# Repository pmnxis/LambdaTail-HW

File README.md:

# LambdaTail PCB

**Open source IoT node for arcade game**

The goal of this repository is to make **Rust** + **RISC-V** + **Kicad6** based hardware.
And IoT node should be published to large number of devices. So aimed to manufacture with low-cost with less-BOM.

## How works
Monitor vend side device such as paper or coin acceptor at top connector. And then reflect or modify signal to bottom side's connector. 

While monitor vend side, send signal to server or process something.

## Schematics
[Schematic](doc/LambdaTail-HW.pdf)

## Simplified characteristics
| Parameter | Min | Typ | Max | Unit | 
| --- | --- | --- | --- | --- |
| Voltage Power Supply | 4.5 | 12  | 16  | V  |
| Current Consumption  | 50  | 100 | 400 | mA |
| Dimenssion | | 55 x 55 x 16 | | mm

## Dependancy of footprint library
 - https://github.com/pmnxis/Lambda_KICAD5_LIB
 - https://github.com/espressif/kicad-libraries
 - Kicad 5.99 (Kicad 6) and Kicad 5 (legacy) default libraries.

## License
CERN-OHL-S-2.0 for Routing, Gerber, Schematic

Follow to original owner's license for footprint and related things.

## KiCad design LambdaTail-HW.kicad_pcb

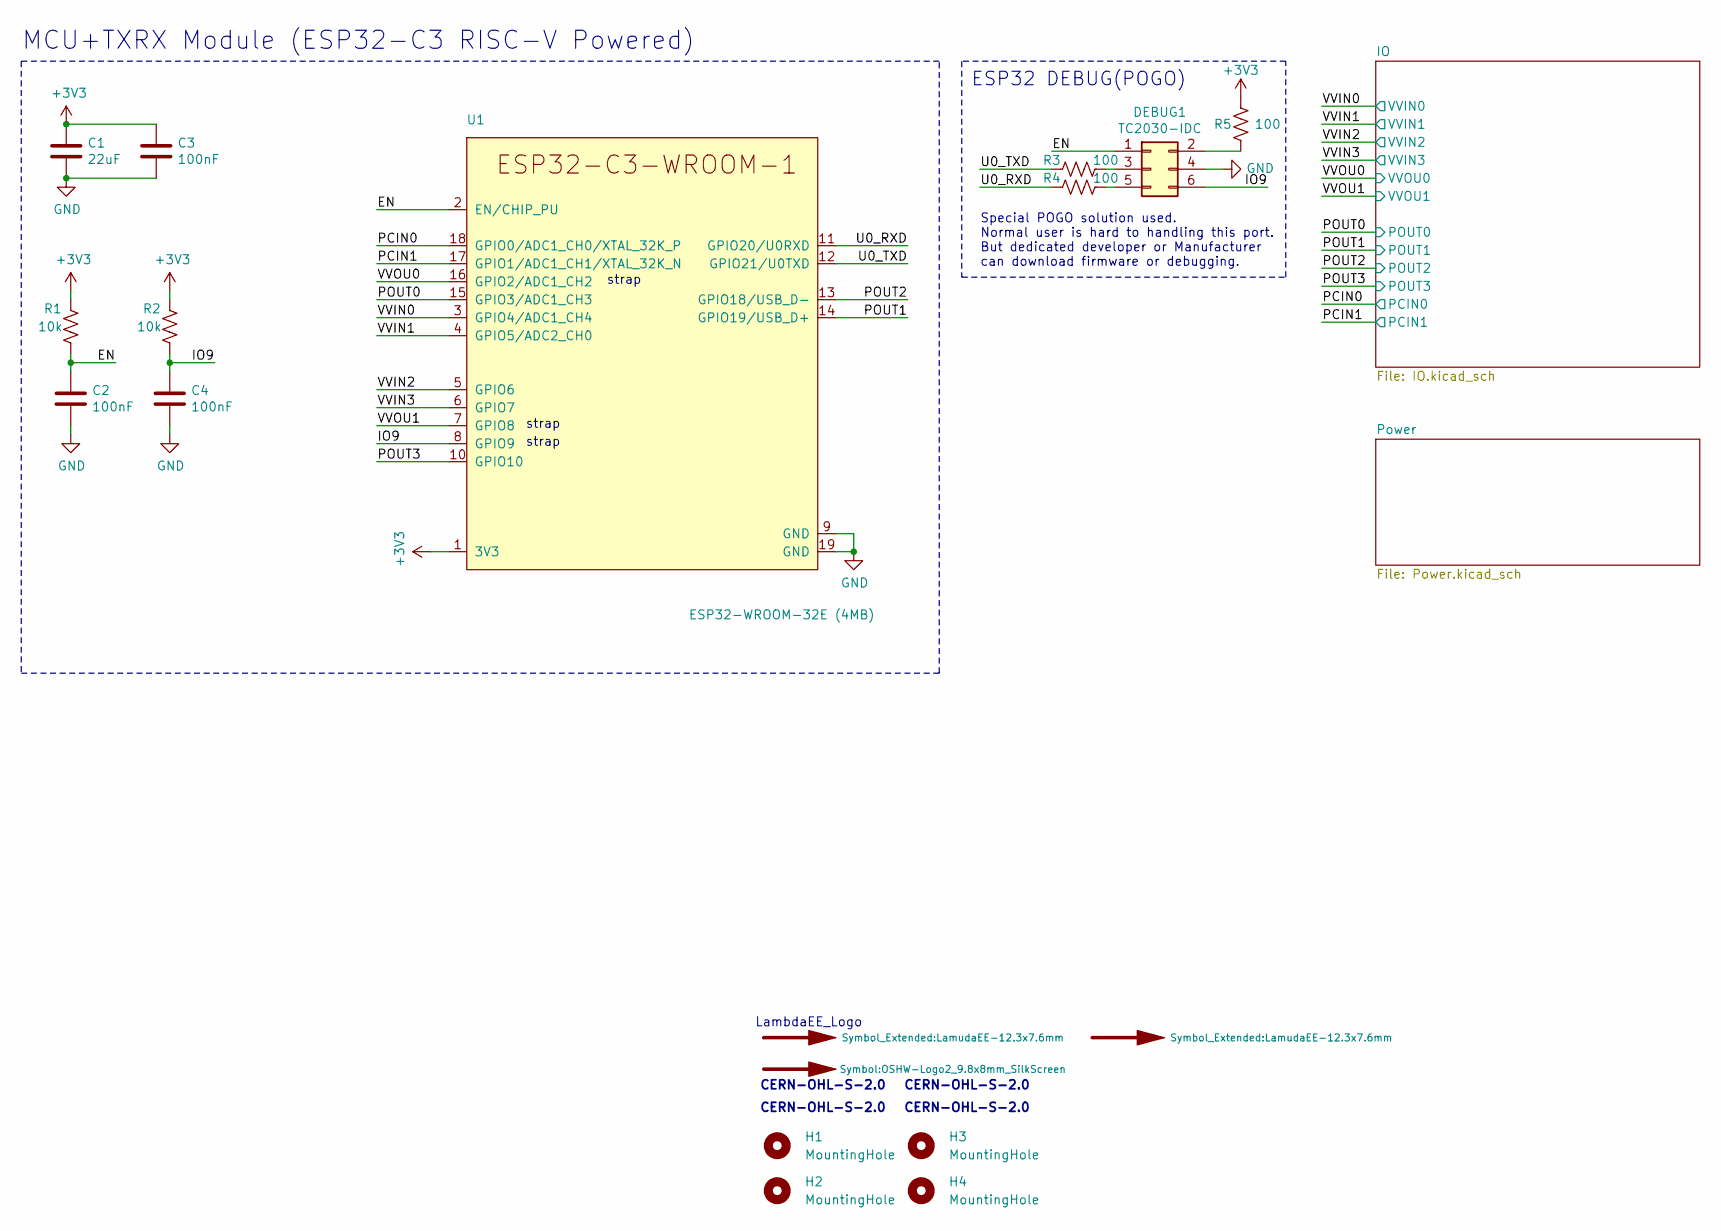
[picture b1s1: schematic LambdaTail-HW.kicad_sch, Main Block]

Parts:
C1: 22uF; C_0805_2012Metric; MFR.Part# CL21A226MAQNNNE; LCSC Part C45783
C2, C3, C4: 100nF; C_0402_1005Metric; MFR.Part# CL05B104KO5NNNC; LCSC Part C1525
DEBUG1: TC2030-IDC; Tag-Connect_TC2030-IDC-FP_2x03_P1.27mm_Vertical
H1, H2, H3, H4: MountingHole; MountingHole_4.3mm_M4_ISO7380_Pad_TopBottom
R1, R2: 10k; R_0402_1005Metric; MFR.Part# 0402WGF1002TCE; LCSC Part C25744
R3, R4, R5: 100; R_0402_1005Metric; MFR.Part# 0402WGF1000TCE; LCSC Part C25076
SYM1, SYM3: SYM_Arrow_XLarge; LamudaEE-12.3x7.6mm
SYM2: SYM_Arrow_XLarge; OSHW-Logo2_9.8x8mm_SilkScreen
U1: ESP32-WROOM-32E (4MB); ESP32-C3-WROOM-1; MFR.Part# ESP32-WROOM-32E (4MB)

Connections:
/EN: C2.1, DEBUG1.1, R1.2, U1.2 (EN/CHIP_PU)
/IO9: C4.1, DEBUG1.6, R2.2, U1.8 (GPIO9)
/PCIN0: U1.18 (GPIO0/ADC1_CH0/XTAL_32K_P); also elsewhere on the board
/PCIN1: U1.17 (GPIO1/ADC1_CH1/XTAL_32K_N); also elsewhere on the board
/POUT0: U1.15 (GPIO3/ADC1_CH3); also elsewhere on the board
/POUT1: U1.14 (GPIO19/USB_D+); also elsewhere on the board
/POUT2: U1.13 (GPIO18/USB_D-); also elsewhere on the board
/POUT3: U1.10 (GPIO10); also elsewhere on the board
/U0_RXD: R4.1, U1.11 (GPIO20/U0RXD)
/U0_TXD: R3.1, U1.12 (GPIO21/U0TXD)
/VVIN0: U1.3 (GPIO4/ADC1_CH4); also elsewhere on the board
/VVIN1: U1.4 (GPIO5/ADC2_CH0); also elsewhere on the board
/VVIN2: U1.5 (GPIO6); also elsewhere on the board
/VVIN3: U1.6 (GPIO7); also elsewhere on the board
/VVOU0: U1.16 (GPIO2/ADC1_CH2); also elsewhere on the board
/VVOU1: U1.7 (GPIO8); also elsewhere on the board
GND: C1.2, C2.2, C3.2, C4.2, DEBUG1.4, U1.9 (GND), U1.19 (GND); also elsewhere on the board
unnamed: DEBUG1.2, R5.2
unnamed: DEBUG1.3, R3.2
unnamed: DEBUG1.5, R4.2

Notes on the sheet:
MCU+TXRX Module (ESP32-C3 RISC-V Powered)
strap
LambdaEE_Logo
CERN-OHL-S-2.0
ESP32 DEBUG(POGO)
Special POGO solution used. Normal user is hard to handling this port. But dedicated developer or Manufacturer can download firmware or debugging.

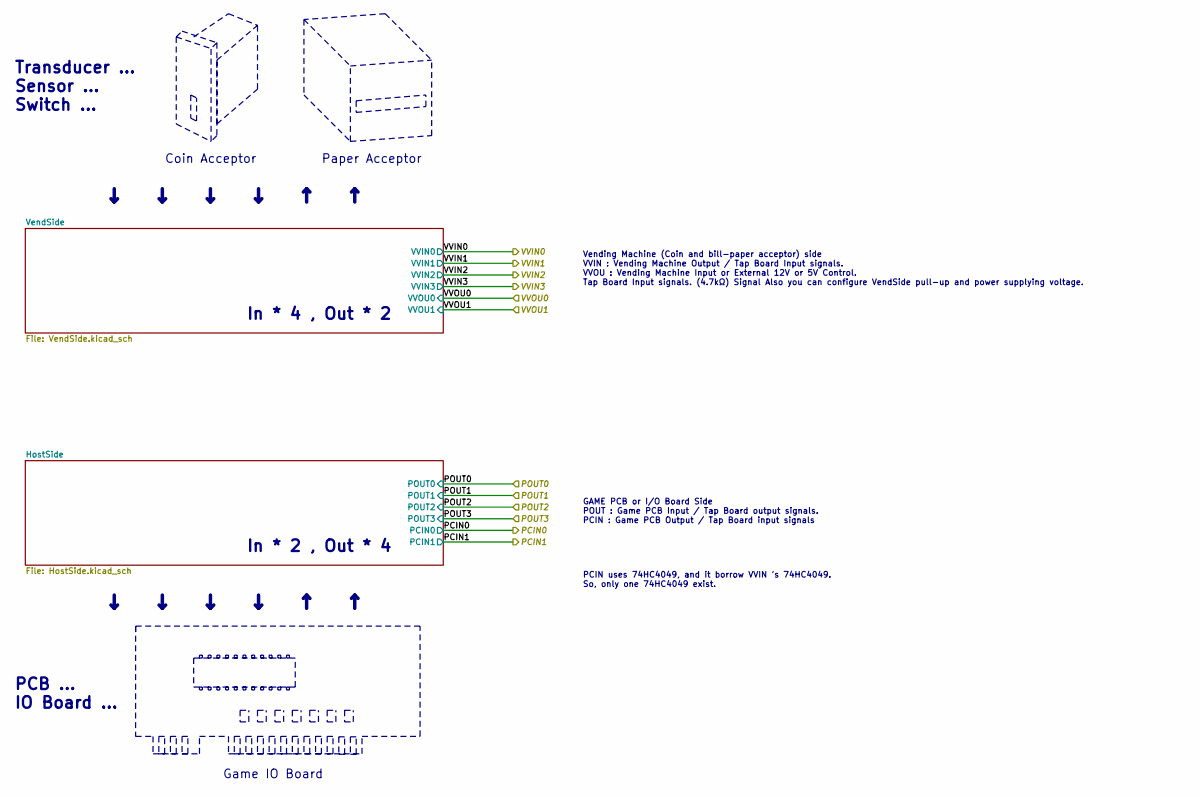
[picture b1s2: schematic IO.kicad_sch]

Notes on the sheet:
Transducer ... Sensor ... Switch ...
PCB ... IO Board ...
Coin Acceptor
Game IO Board
In * 4 , Out * 2
In * 2 , Out * 4
Paper Acceptor
↓ ↓ ↓ ↓ ↑ ↑
Vending Machine (Coin and bill-paper acceptor) side VVIN : Vending Machine Output / Tap Board Input signals. VVOU : Vending Machine Input or External 12V or 5V Control. Tap Board Input signals. (4.7kΩ) Signal Also you can configure VendSide pull-up and power supplying voltage.
GAME PCB or I/O Board Side POUT : Game PCB Input / Tap Board output signals. PCIN : Game PCB Output / Tap Board input signals
PCIN uses 74HC4049, and it borrow VVIN 's 74HC4049. So, only one 74HC4049 exist.

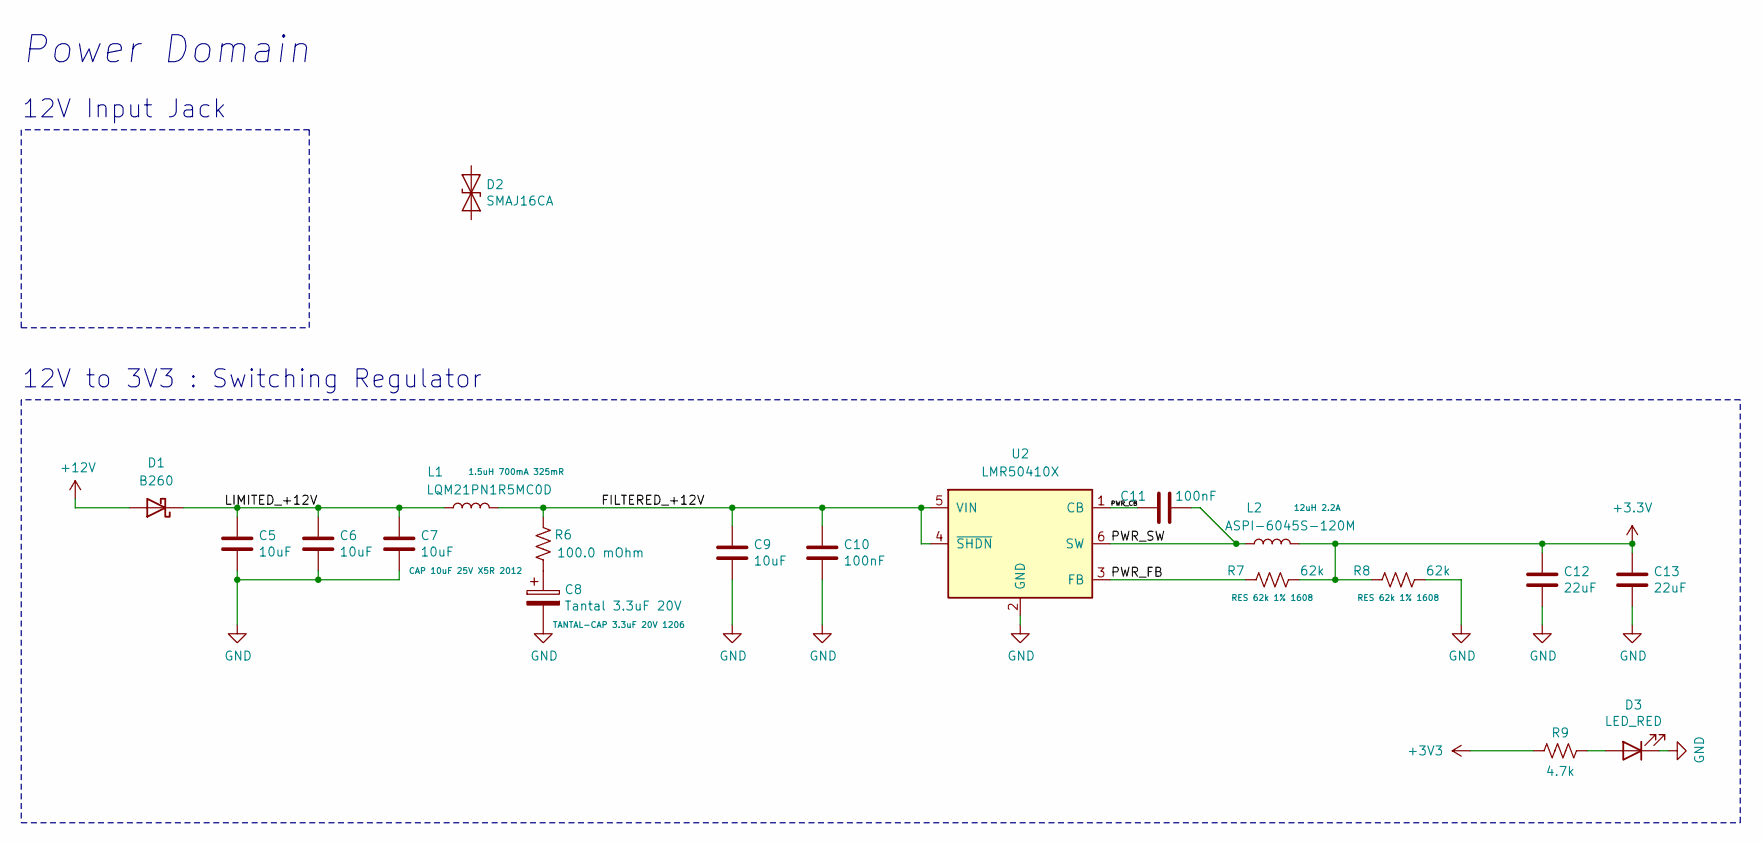
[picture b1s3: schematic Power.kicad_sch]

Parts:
C5, C6, C7, C9: 10uF; C_0805_2012Metric; MFR.Part# GRM31CR61E106KA12L; LCSC Part C15850
C8: Tantal 3.3uF 20V; CP_EIA-3216-18_Kemet-A; MFR.Part# TPSA335K020R2500; LCSC Part xx
C10, C11: 100nF; C_0402_1005Metric; MFR.Part# CL05B104KO5NNNC; LCSC Part C1525
C12, C13: 22uF; C_0805_2012Metric; MFR.Part# CL21A226MAQNNNE; LCSC Part C45783
D1: B260; D_SMB
D2: SMAJ16CA; D_SMA; MFR.Part# SMAJ16CA; LCSC Part C135970
D3: LED_RED; LED_0805_2012Metric; MFR.Part# FC-2012HRK-620D; LCSC Part C84256
L1: LQM21PN1R5MC0D; L_0805_2012Metric; MFR.Part# LQM21PN1R5MC0D; LCSC Part C184208
L2: ASPI-6045S-120M; L_TDK_VLS6045EX; MFR.Part# ASPI-6045S-120M; LCSC Part C187451
R6: 100.0 mOhm; R_0402_1005Metric; MFR.Part# 0402WGF4701TCE; LCSC Part C25900
R7, R8: 62k; R_0603_1608Metric; MFR.Part# 0603WAF6202T5E; LCSC Part C23221
R9: 4.7k; R_0402_1005Metric; MFR.Part# 0402WGF4701TCE; LCSC Part C25900
U2: LMR50410X; SOT-23-6

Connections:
+12V: D1.2 (A); also elsewhere on the board
/Power/FILTERED_+12V: C9.1, C10.1, L1.2, R6.2, U2.4 (~SHDN), U2.5 (VIN)
/Power/LIMITED_+12V: C5.1, C6.1, C7.1, D1.1 (K), L1.1
/Power/PWR_CB: C11.1, U2.1 (CB)
/Power/PWR_FB: R7.1, U2.3 (FB)
/Power/PWR_SW: C11.2, L2.1, U2.6 (SW)
GND: C5.2, C6.2, C7.2, C8.2, C9.2, C10.2, C12.2, C13.2, D3.1 (K), R8.2, U2.2 (GND); also elsewhere on the board
unnamed: C8.1, R6.1
unnamed: D3.2 (A), R9.2

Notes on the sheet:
Power Domain
12V Input Jack
12V to 3V3 : Switching Regulator

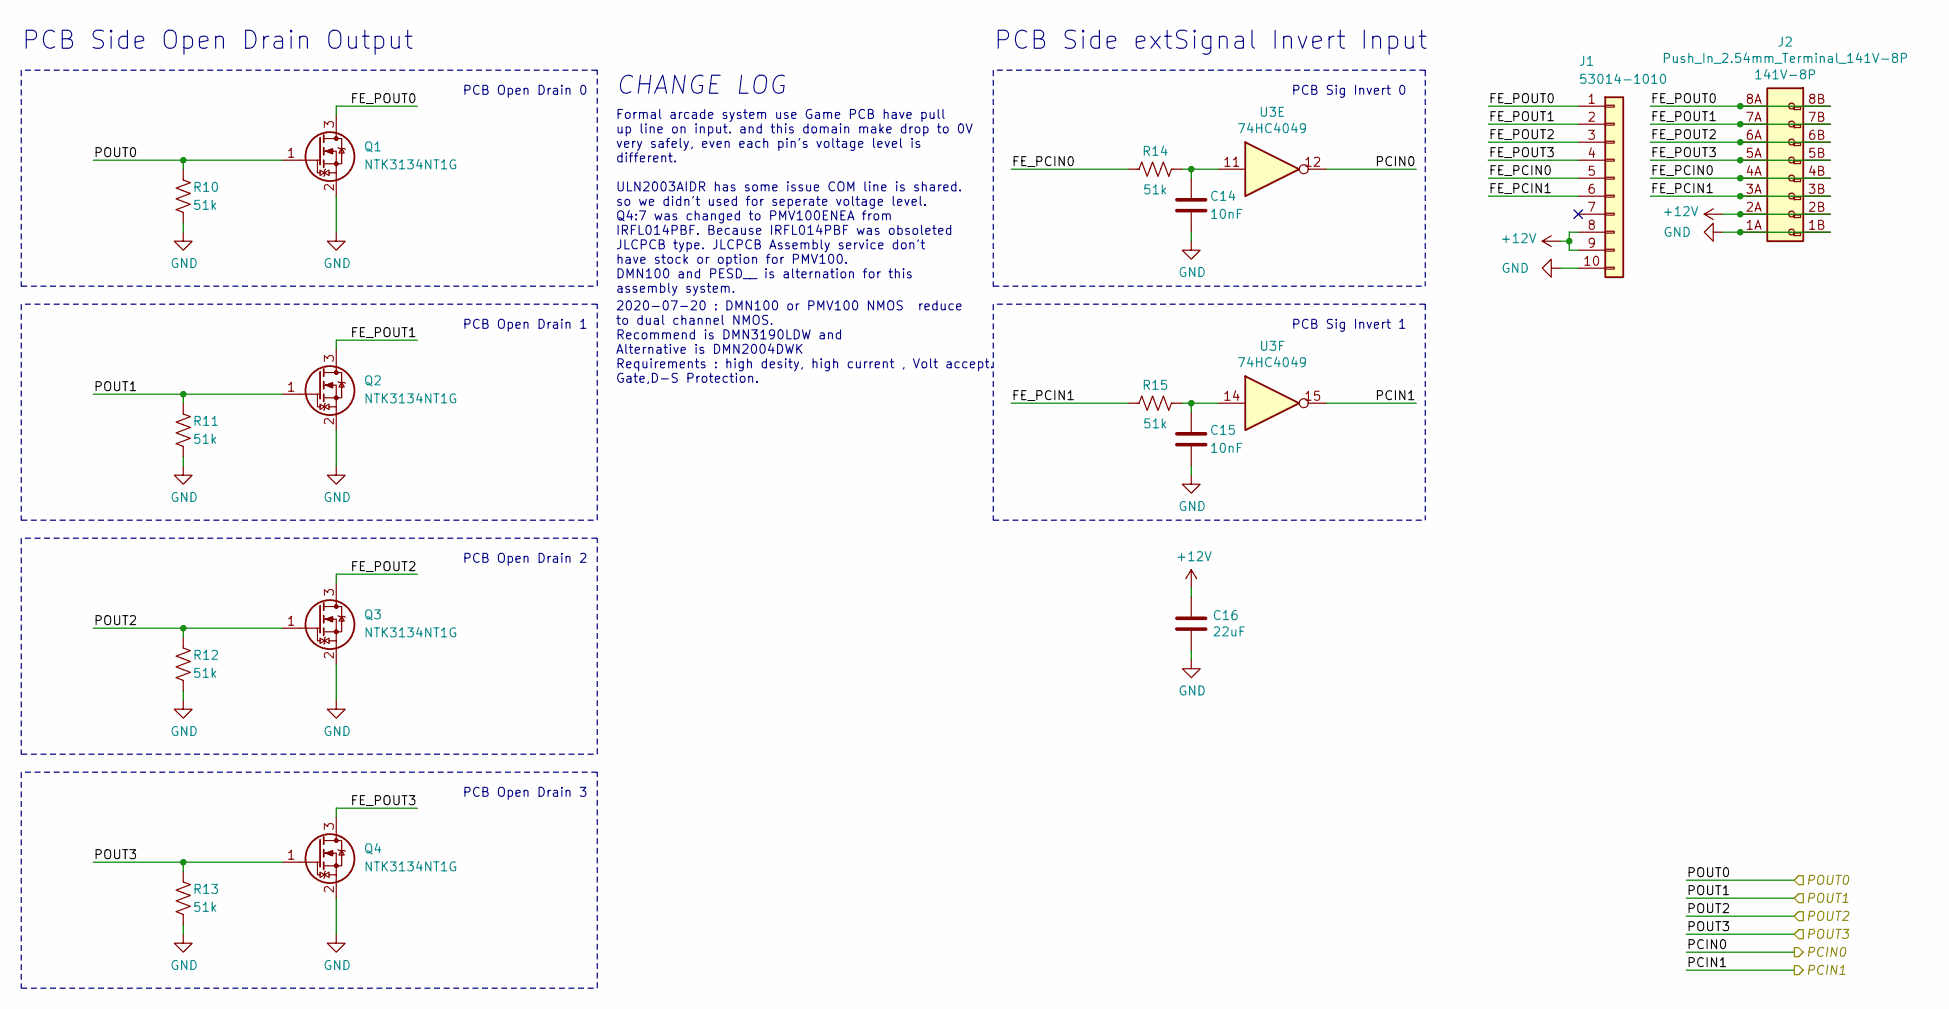
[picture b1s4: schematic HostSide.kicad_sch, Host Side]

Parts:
C14, C15: 10nF; C_0402_1005Metric; MFR.Part# CL05B103KB5NNNC; LCSC Part C15195
C16: 22uF; C_0805_2012Metric; MFR.Part# CL21A226MAQNNNE; LCSC Part C45783
J1: 53014-1010; Molex_MicroBlade_53014-1000_1x10_P2.00mm_Vertical; MFR.Part# 53014-1010
J2: Push_In_2.54mm_Terminal_141V-8P; TERMINAL_141V-8P; MFR.Part# 141V-8P
Q1, Q2, Q3, Q4: NTK3134NT1G; SOT-723; MFR.Part# NTK3134NT1G; LCSC Part C97777
R10, R11, R12, R13, R14, R15: 51k; R_0402_1005Metric; MFR.Part# 0402WGF5102TCE; LCSC Part C25794
U3: 74HC4049; TSSOP-16_4.4x5mm_P0.65mm; MFR.Part# MC14049UBDTR2GOS

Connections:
+12V: C16.1, J1.8, J1.9, J2.2A, J2.2B; also elsewhere on the board
/IO/HostSide/FE_PCIN0: J1.5, J2.4A, J2.4B, R14.1
/IO/HostSide/FE_PCIN1: J1.6, J2.3A, J2.3B, R15.1
/IO/HostSide/FE_POUT0: J1.1, J2.8A, J2.8B, Q1.3 (D)
/IO/HostSide/FE_POUT1: J1.2, J2.7A, J2.7B, Q2.3 (D)
/IO/HostSide/FE_POUT2: J1.3, J2.6A, J2.6B, Q3.3 (D)
/IO/HostSide/FE_POUT3: J1.4, J2.5A, J2.5B, Q4.3 (D)
/PCIN0: U3.12; also elsewhere on the board
/PCIN1: U3.15; also elsewhere on the board
/POUT0: Q1.1 (G), R10.1; also elsewhere on the board
/POUT1: Q2.1 (G), R11.1; also elsewhere on the board
/POUT2: Q3.1 (G), R12.1; also elsewhere on the board
/POUT3: Q4.1 (G), R13.1; also elsewhere on the board
GND: C14.2, C15.2, C16.2, J1.10, J2.1A, J2.1B, Q1.2 (S), Q2.2 (S), Q3.2 (S), Q4.2 (S), R10.2, R11.2, R12.2, R13.2; also elsewhere on the board
unnamed: C14.1, R14.2, U3.11
unnamed: C15.1, R15.2, U3.14

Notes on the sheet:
PCB Side Open Drain Output
PCB Open Drain 0
PCB Open Drain 1
PCB Open Drain 2
PCB Open Drain 3
CHANGE LOG
Formal arcade system use Game PCB have pull up line on input. and this domain make drop to 0V very safely, even each pin's voltage level is different. ULN2003AIDR has some issue COM line is shared. so we didn't used for seperate voltage level. Q4:7 was changed to PMV100ENEA from IRFL014PBF. Because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
2020-07-20 : DMN100 or PMV100 NMOS reduce to dual channel NMOS. Recommend is DMN3190LDW and Alternative is DMN2004DWK Requirements : high desity, high current , Volt accept. Gate,D-S Protection.
PCB Side extSignal Invert Input
PCB Sig Invert 0
PCB Sig Invert 1

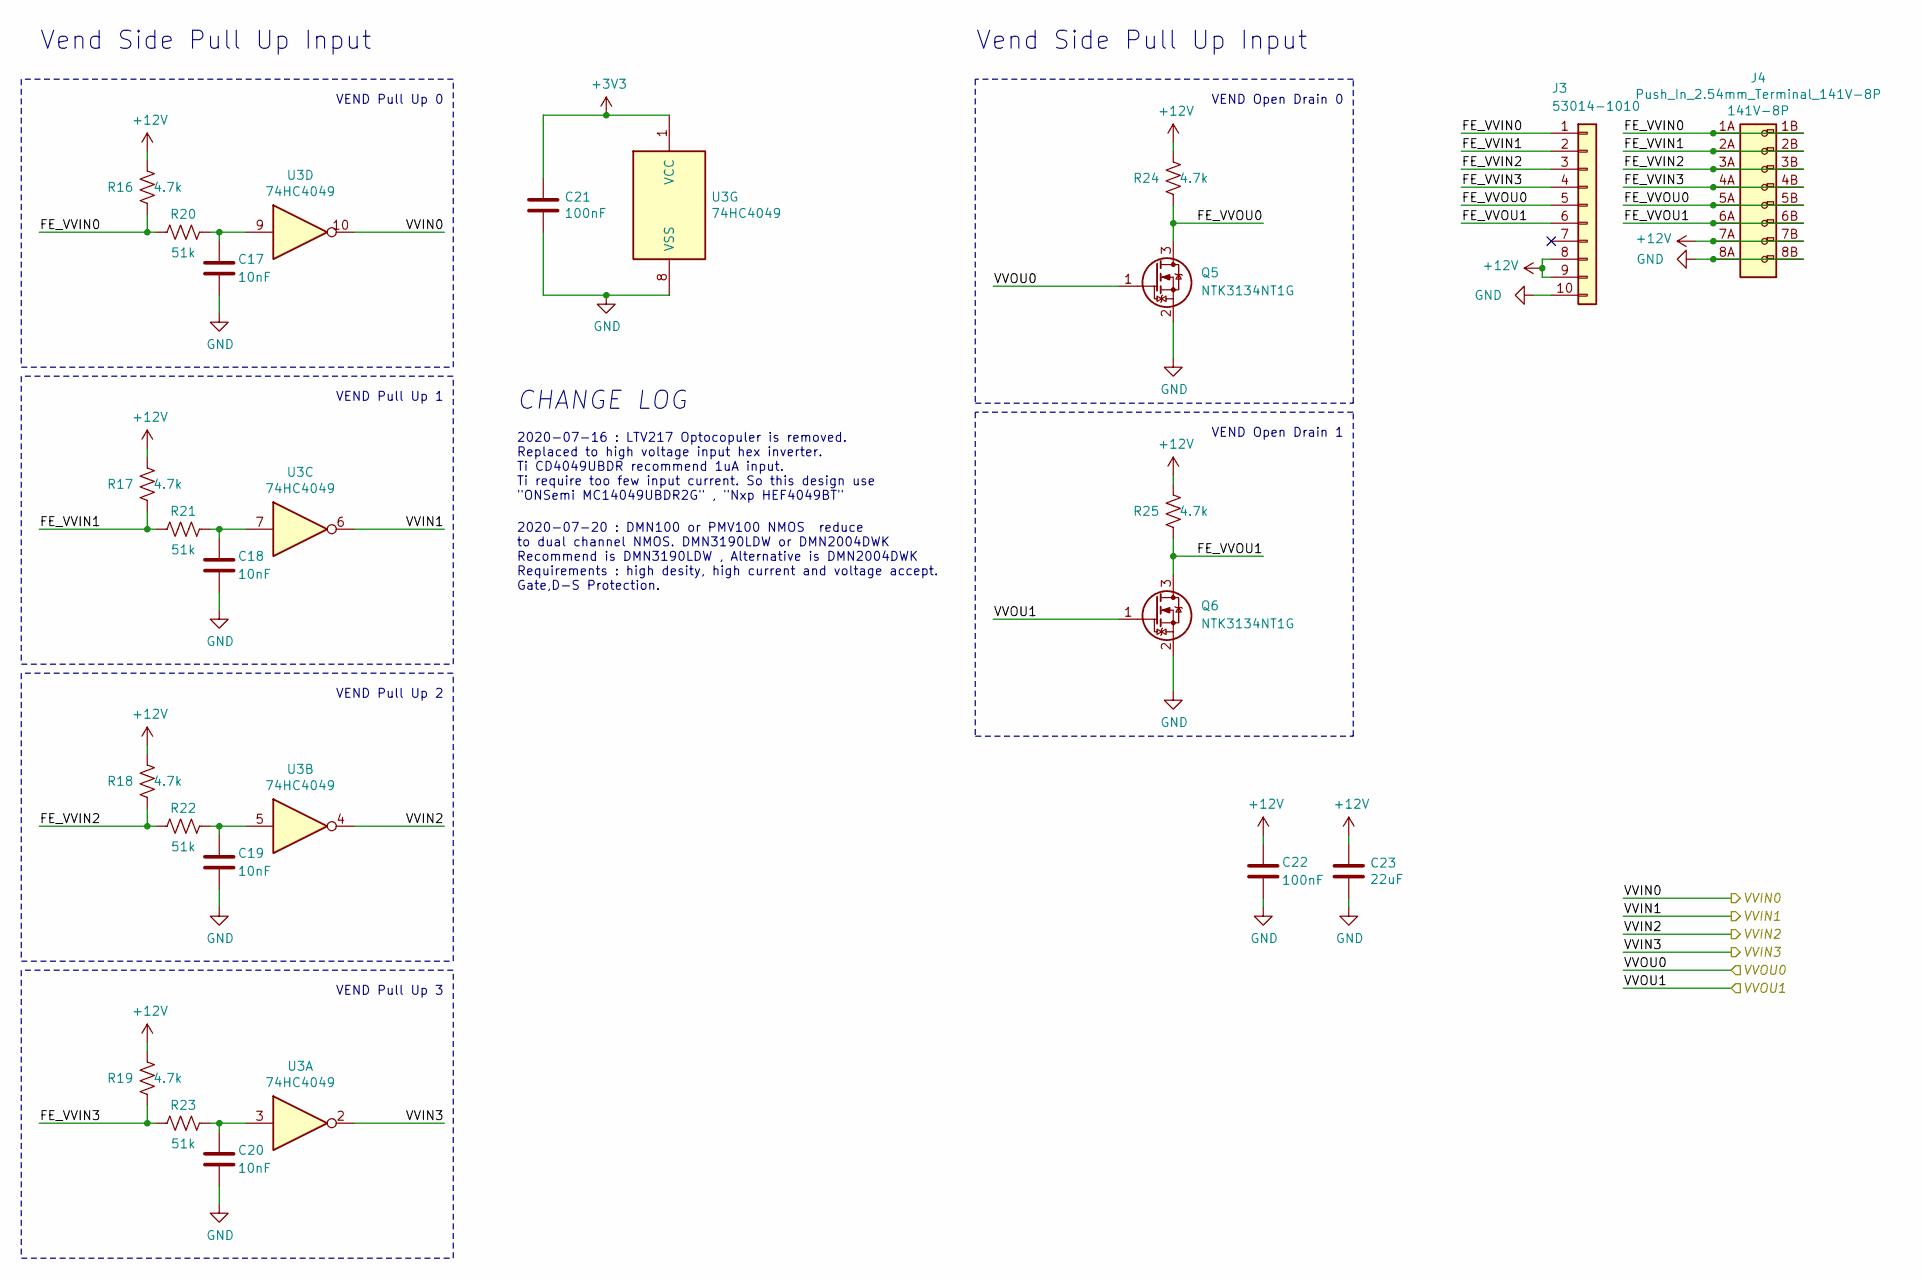
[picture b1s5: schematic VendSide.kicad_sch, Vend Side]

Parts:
C17, C18, C19, C20: 10nF; C_0402_1005Metric; MFR.Part# CL05B103KB5NNNC; LCSC Part C15195
C21, C22: 100nF; C_0402_1005Metric; MFR.Part# CL05B104KO5NNNC; LCSC Part C1525
C23: 22uF; C_0805_2012Metric; MFR.Part# CL21A226MAQNNNE; LCSC Part C45783
J3: 53014-1010; Molex_MicroBlade_53014-1000_1x10_P2.00mm_Vertical; MFR.Part# 53014-1010
J4: Push_In_2.54mm_Terminal_141V-8P; TERMINAL_141V-8P; MFR.Part# 141V-8P
Q5, Q6: NTK3134NT1G; SOT-723; MFR.Part# NTK3134NT1G; LCSC Part C97777
R16, R17, R18, R19, R24, R25: 4.7k; R_0402_1005Metric; MFR.Part# 0402WGF4701TCE; LCSC Part C25900
R20, R21, R22, R23: 51k; R_0402_1005Metric; MFR.Part# 0402WGF5102TCE; LCSC Part C25794
U3: 74HC4049; TSSOP-16_4.4x5mm_P0.65mm; MFR.Part# MC14049UBDTR2GOS

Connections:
+12V: C22.1, C23.1, J3.8, J3.9, J4.7A, J4.7B, R16.2, R17.2, R18.2, R19.2, R24.2, R25.2; also elsewhere on the board
/IO/VendSide/FE_VVIN0: J3.1, J4.1A, J4.1B, R16.1, R20.1
/IO/VendSide/FE_VVIN1: J3.2, J4.2A, J4.2B, R17.1, R21.1
/IO/VendSide/FE_VVIN2: J3.3, J4.3A, J4.3B, R18.1, R22.1
/IO/VendSide/FE_VVIN3: J3.4, J4.4A, J4.4B, R19.1, R23.1
/IO/VendSide/FE_VVOU0: J3.5, J4.5A, J4.5B, Q5.3 (D), R24.1
/IO/VendSide/FE_VVOU1: J3.6, J4.6A, J4.6B, Q6.3 (D), R25.1
/VVIN0: U3.10; also elsewhere on the board
/VVIN1: U3.6; also elsewhere on the board
/VVIN2: U3.4; also elsewhere on the board
/VVIN3: U3.2; also elsewhere on the board
/VVOU0: Q5.1 (G); also elsewhere on the board
/VVOU1: Q6.1 (G); also elsewhere on the board
GND: C17.2, C18.2, C19.2, C20.2, C21.2, C22.2, C23.2, J3.10, J4.8A, J4.8B, Q5.2 (S), Q6.2 (S), U3.8 (VSS); also elsewhere on the board
unnamed: C17.1, R20.2, U3.9
unnamed: C18.1, R21.2, U3.7
unnamed: C19.1, R22.2, U3.5
unnamed: C20.1, R23.2, U3.3

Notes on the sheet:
Vend Side Pull Up Input
VEND Pull Up 0
VEND Pull Up 1
VEND Pull Up 2
VEND Pull Up 3
CHANGE LOG
2020-07-16 : LTV217 Optocopuler is removed. Replaced to high voltage input hex inverter. Ti CD4049UBDR recommend 1uA input. Ti require too few input current. So this design use "ONSemi MC14049UBDR2G" , "Nxp HEF4049BT"
2020-07-20 : DMN100 or PMV100 NMOS reduce to dual channel NMOS. DMN3190LDW or DMN2004DWK Recommend is DMN3190LDW , Alternative is DMN2004DWK Requirements : high desity, high current and voltage accept. Gate,D-S Protection.
VEND Open Drain 0
VEND Open Drain 1

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
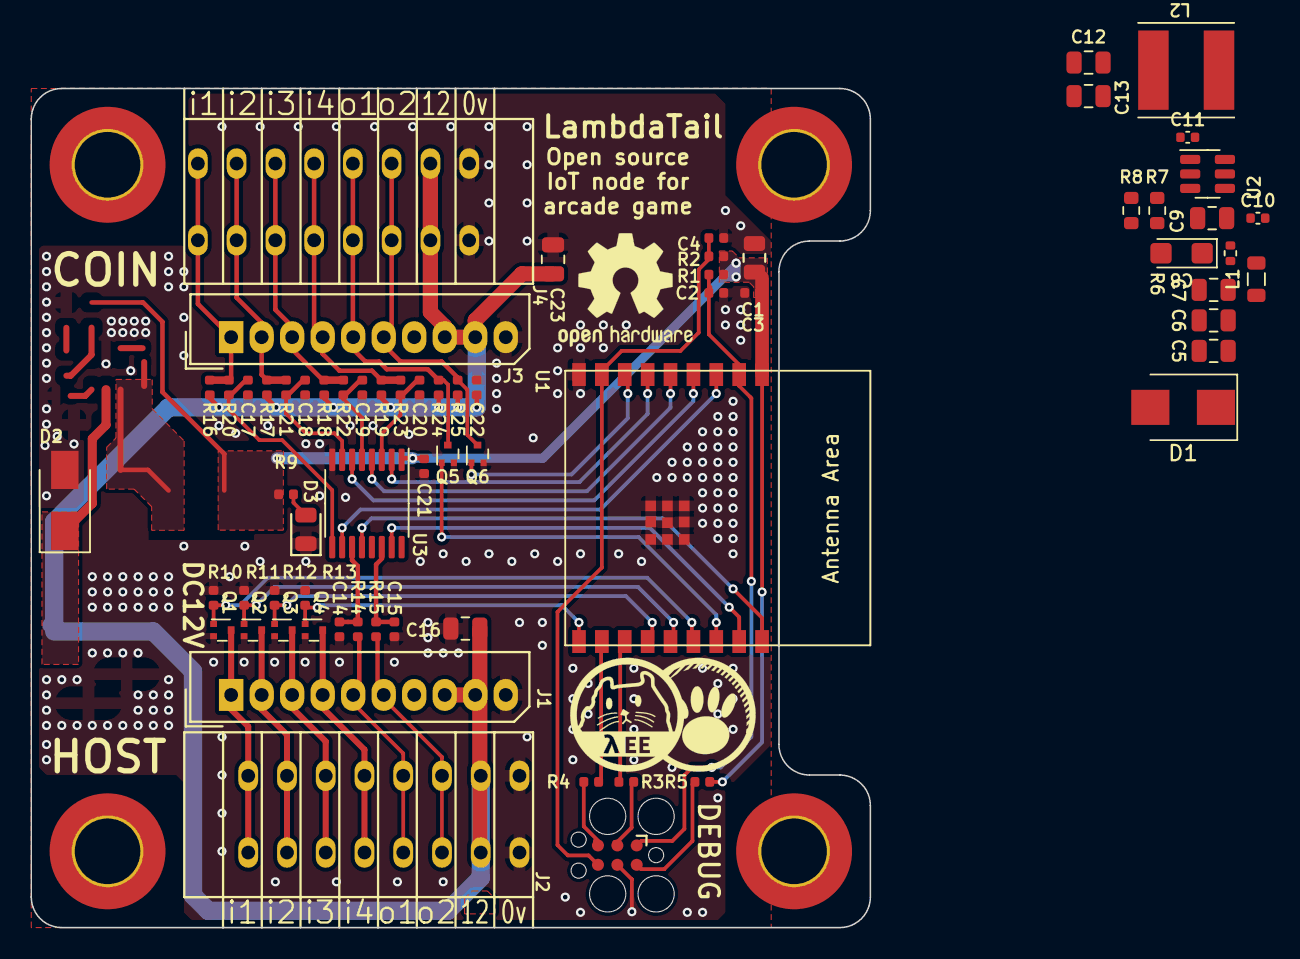
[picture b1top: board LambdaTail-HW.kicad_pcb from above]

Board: 2 copper layers, 55.0 x 55.0 mm, 74 parts (1 on the bottom side), 47 nets.

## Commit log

2021-07-19 First release
2021-07-19 update sch
2021-10-28 init to 0.2
